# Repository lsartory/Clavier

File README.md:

# Clavier

Clavier (French for ‘keyboard’) is an FPGA-based mechanical keyboard with an integrated USB hub, and numerous communication interfaces (JTAG, SPI, I²C, UART).

## Features

- Full size 105 keys ISO keyboard + one extra
- Compatible with PCB mounted Cherry MX switches
- N-key rollover
- 1000 Hz polling rate
- No multiplexing, no ghosting
- 2-port USB 2.0 hub
- JTAG, SPI, I²C, 2 × UART, and 8 × GPIOs
- FPGA-based, VHDL only, no ALU
- Fully open-source, including all design tools (see below)

### What's the extra key for?

It's the coffee key.
Use it to lock your computer and go have a break.

It can also be long-pressed for 5 seconds to reset the FPGA.

## Required tools

- [KiCad](https://www.kicad.org) for the PCB
- [FreeCAD](https://www.freecad.org) or [OpenSCAD](https://openscad.org) for the housing
- [OSS CAD Suite](https://github.com/YosysHQ/oss-cad-suite-build) (GHDL, Yosys, hdl, ghdl-yosys-plugin, nextpnr-ecp5, ecppack, and openFPGALoader) and [GNU Make](https://www.gnu.org/software/make) for the FPGA

## PCB

The PCB has 4 layers and requires no unusual capabilities to produce.
It is however not easy to assemble by hand mostly due to 0402 passives and the FPGA in BGA packaging.

### Schematics

A PDF version of the schematics is available here, for convenience: [PCB/doc/clavier.pdf](PCB/doc/clavier.pdf).

## Housing

### Version 1

An OpenSCAD version of the housing was created first and is fine for 3D printing.
The FreeCAD version was created afterwards for exporting to STEP, which is more suitable for CNC machining.
Both alternatives are functionally equivalent.

### Version 2

The first version fits properly, but it turns out that it is not angled in a comfortable way.
To correct this, a second version was created with an angle of 8° that makes the front part much thinner.
This one is only available in FreeCAD.

## FPGA

### How to build

Simply run `make` in the FPGA subfolder.
If using OSS CAD Suite, make sure [the environment is set](https://github.com/YosysHQ/oss-cad-suite-build?tab=readme-ov-file#installation) first.

### How to program

The integrated JTAG interface can be used to program the FPGA.
The switch `SW18` is used to toggle the interfaces on or off. The LED `D1` close by displays the current status.
Connect the JTAG interface with jumper cables, then run either `make prog-sram` or `make prog-flash`, depending on if the configuration needs to be permanent or not.

## Communication interfaces

Except for the GPIOs that are connected directly to the FPGA, communications are handled by the [CH347F](https://www.lcsc.com/datasheet/C18221627.pdf).

## 3D renders

## Licenses

- The PCB and housing are licensed under the [CERN Open Hardware Licence Version 2 - Permissive](https://spdx.org/licenses/CERN-OHL-P-2.0.html).
- The FPGA code is licensed under the [MIT Licence](https://spdx.org/licenses/MIT.html).
- The pictures are licensed under the [CC BY 4.0 License](https://creativecommons.org/licenses/by/4.0/).

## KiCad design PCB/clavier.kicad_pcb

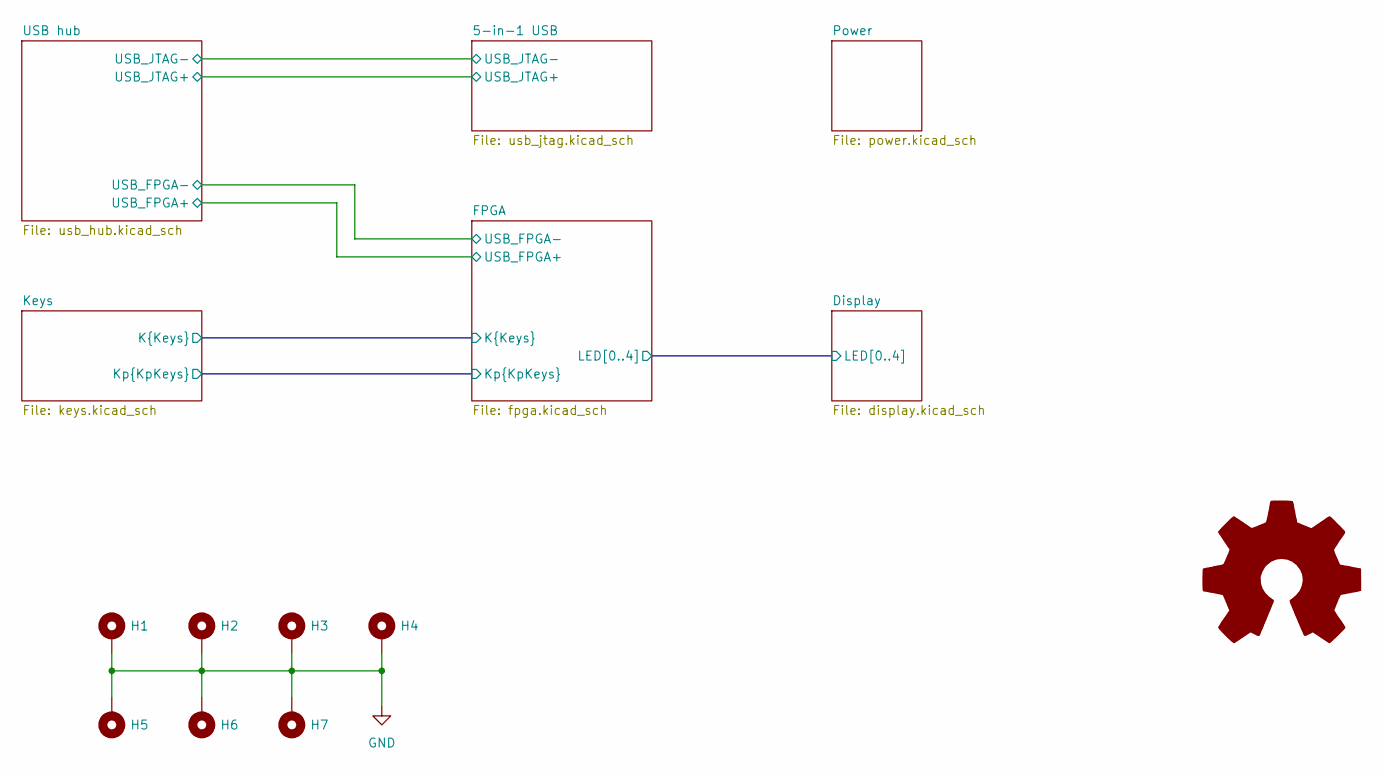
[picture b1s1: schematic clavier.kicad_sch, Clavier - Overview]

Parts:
H1, H2, H3, H4, H5, H6, H7: MountingHole_Pad; MountingHole_3.2mm_M3_ISO7380_Pad_TopBottom
OSHW1: Logo_Open_Hardware_Large; OSHW-Symbol_13.4x12mm_SilkScreen

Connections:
GND: H1.1, H2.1, H3.1, H4.1, H5.1, H6.1, H7.1; also elsewhere on the board

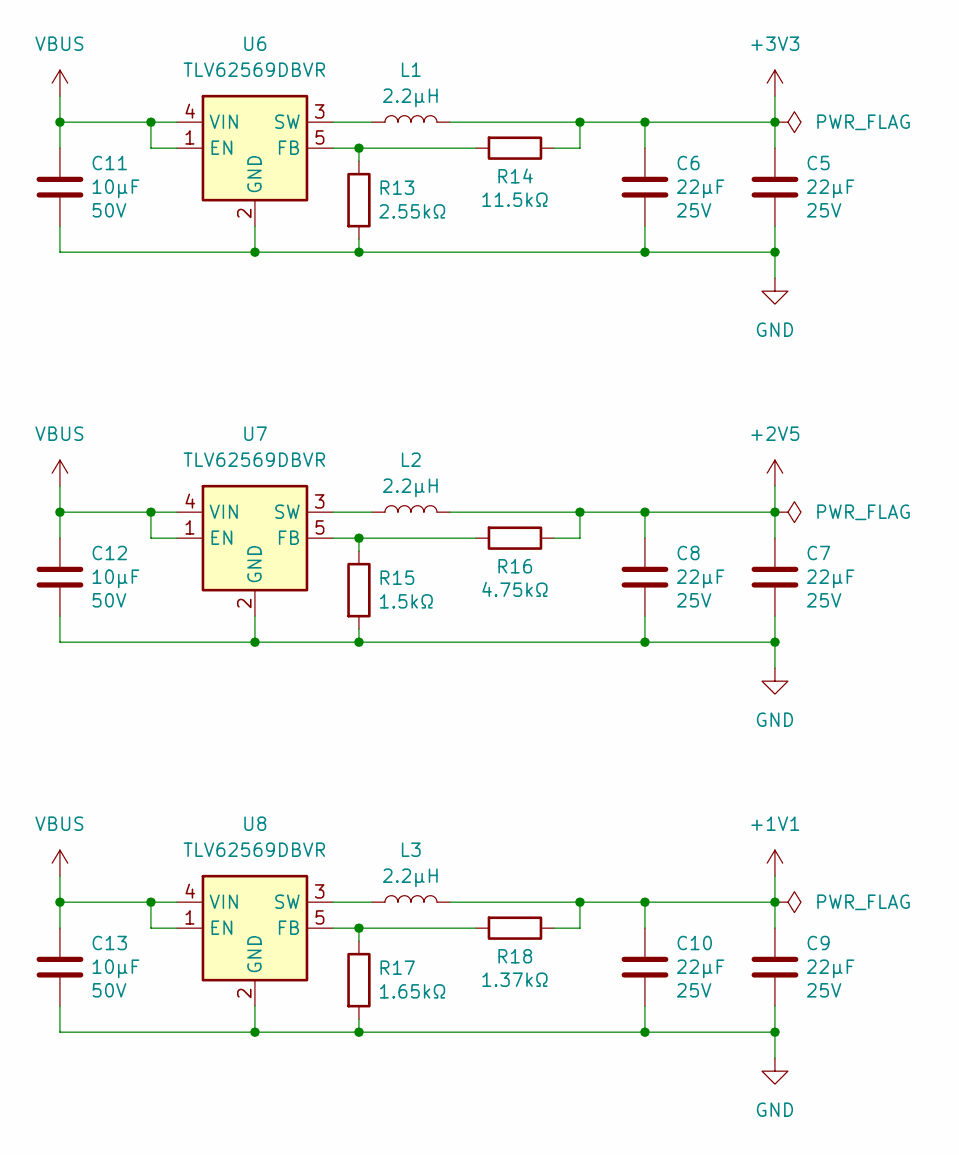
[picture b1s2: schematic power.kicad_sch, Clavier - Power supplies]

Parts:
C5, C6, C7, C8, C9, C10: 22µF; C_0805_2012Metric; Voltage 25V; Part_number GRM21BR61E226ME44L; LCSC C86816
C11, C12, C13: 10µF; C_0805_2012Metric; Voltage 50V; Part_number GRM21BR61H106KE43L; LCSC C440198
L1, L2, L3: 2.2µH; L_1210_3225Metric; Part_number DFE322520FD-2R2M=P2; LCSC C2045365
R13: 2.55kΩ; R_0402_1005Metric_Pad0.72x0.64mm_HandSolder; Part_number RC0402FR-072K55L; LCSC C185431
R14: 11.5kΩ; R_0402_1005Metric_Pad0.72x0.64mm_HandSolder; Part_number RC0402FR-0711K5L; LCSC C295874
R15: 1.5kΩ; R_0402_1005Metric_Pad0.72x0.64mm_HandSolder; Part_number RC0402FR-071K5L; LCSC C114759
R16: 4.75kΩ; R_0402_1005Metric_Pad0.72x0.64mm_HandSolder; Part_number RC0402FR-074K75L; LCSC C137966
R17: 1.65kΩ; R_0402_1005Metric_Pad0.72x0.64mm_HandSolder; Part_number RT0402BRD071K65L; LCSC C852615
R18: 1.37kΩ; R_0402_1005Metric_Pad0.72x0.64mm_HandSolder; Part_number RT0402CRE071K37L; LCSC C705664
U6, U7, U8: TLV62569DBVR; SOT-23-5; Part_number TLV62569DBVR; LCSC C141836

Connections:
+1V1: C9.1, C10.1, L3.2, R18.1; also elsewhere on the board
+2V5: C7.1, C8.1, L2.2, R16.1; also elsewhere on the board
+3V3: C5.1, C6.1, L1.2, R14.1; also elsewhere on the board
GND: C5.2, C6.2, C7.2, C8.2, C9.2, C10.2, C11.2, C12.2, C13.2, R13.2, R15.2, R17.2, U6.2 (GND), U7.2 (GND), U8.2 (GND); also elsewhere on the board
unnamed: R13.1, R14.2, U6.5 (FB)
unnamed: L1.1, U6.3 (SW)
unnamed: R15.1, R16.2, U7.5 (FB)
unnamed: L2.1, U7.3 (SW)
unnamed: R17.1, R18.2, U8.5 (FB)
unnamed: L3.1, U8.3 (SW)
VBUS: C11.1, C12.1, C13.1, U6.1 (EN), U6.4 (VIN), U7.1 (EN), U7.4 (VIN), U8.1 (EN), U8.4 (VIN); also elsewhere on the board

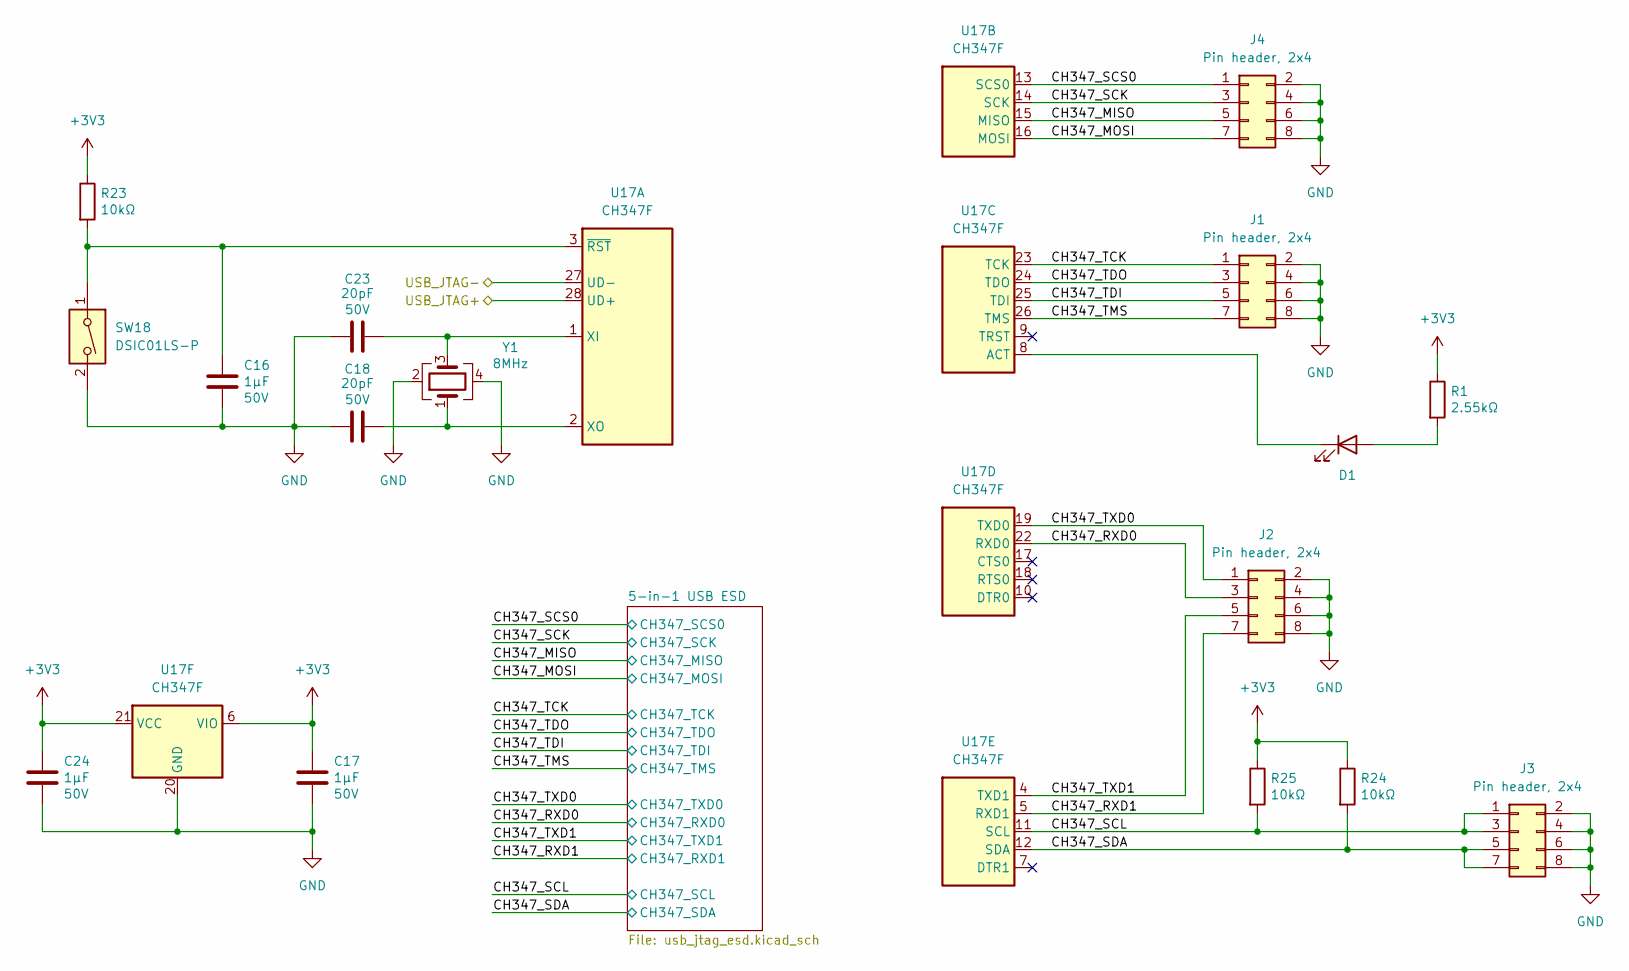
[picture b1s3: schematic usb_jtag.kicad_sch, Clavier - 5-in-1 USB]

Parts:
C16, C17, C24: 1µF; C_0402_1005Metric_Pad0.74x0.62mm_HandSolder; Voltage 50V; Part_number GRM155R61H105KE05D; LCSC C1518208
C18, C23: 20pF; C_0402_1005Metric_Pad0.74x0.62mm_HandSolder; Voltage 50V; Part_number GRM1555C1H200JA01D; LCSC C76959
D1: LED; LED_0603_1608Metric_Pad1.05x0.95mm_HandSolder; Part_number XL-1608UOC-06; LCSC C965800
J1, J2, J3, J4: Pin header, 2x4; PinHeader_2x04_P2.54mm_Vertical; Part_number ZX-PZ2.54-2-4PZZ; LCSC C7501275
R1: 2.55kΩ; R_0402_1005Metric_Pad0.72x0.64mm_HandSolder; Part_number RC0402FR-072K55L; LCSC C185431
R23, R24, R25: 10kΩ; R_0402_1005Metric_Pad0.72x0.64mm_HandSolder; Part_number RE0402DRE0710KL; LCSC C851874
SW18: DSIC01LS-P; SW_DIP_SPSTx01_Slide_6.7x4.1mm_W8.61mm_P2.54mm_LowProfile; Part_number DSIC01LS-P; LCSC C600988
U17: CH347F; QFN-28-1EP_4x4mm_P0.4mm_EP2.4x2.4mm; Part_number CH347F; LCSC C18221627
Y1: 8MHz; Crystal_SMD_3225-4Pin_3.2x2.5mm; Part_number TAXM8M4RDBCCT2T; LCSC C400090

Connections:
+3V3: C17.1, C24.1, R1.1, R23.1, R24.1, R25.1, U17.6 (VIO), U17.21 (VCC); also elsewhere on the board
/5-in-1 USB/CH347_MISO: J4.5, U17.15 (MISO); also elsewhere on the board
/5-in-1 USB/CH347_MOSI: J4.7, U17.16 (MOSI); also elsewhere on the board
/5-in-1 USB/CH347_RXD0: J2.3, U17.22 (RXD0); also elsewhere on the board
/5-in-1 USB/CH347_RXD1: J2.7, U17.5 (RXD1); also elsewhere on the board
/5-in-1 USB/CH347_SCK: J4.3, U17.14 (SCK); also elsewhere on the board
/5-in-1 USB/CH347_SCL: J3.1, J3.3, R25.2, U17.11 (SCL); also elsewhere on the board
/5-in-1 USB/CH347_SCS0: J4.1, U17.13 (SCS0); also elsewhere on the board
/5-in-1 USB/CH347_SDA: J3.5, J3.7, R24.2, U17.12 (SDA); also elsewhere on the board
/5-in-1 USB/CH347_TCK: J1.1, U17.23 (TCK); also elsewhere on the board
/5-in-1 USB/CH347_TDI: J1.5, U17.25 (TDI); also elsewhere on the board
/5-in-1 USB/CH347_TDO: J1.3, U17.24 (TDO); also elsewhere on the board
/5-in-1 USB/CH347_TMS: J1.7, U17.26 (TMS); also elsewhere on the board
/5-in-1 USB/CH347_TXD0: J2.1, U17.19 (TXD0); also elsewhere on the board
/5-in-1 USB/CH347_TXD1: J2.5, U17.4 (TXD1); also elsewhere on the board
/5-in-1 USB/USB_JTAG+: U17.28 (UD+); also elsewhere on the board
/5-in-1 USB/USB_JTAG-: U17.27 (UD-); also elsewhere on the board
GND: C16.2, C17.2, C18.1, C23.1, C24.2, J1.2, J1.4, J1.6, J1.8, J2.2, J2.4, J2.6, J2.8, J3.2, J3.4, J3.6, J3.8, J4.2, J4.4, J4.6, J4.8, SW18.2, U17.20 (GND), U17.29 (GND), Y1.2, Y1.4; also elsewhere on the board
unnamed: D1.2 (A), R1.2
unnamed: D1.1 (K), U17.8 (ACT)
unnamed: C23.2, U17.1 (XI), Y1.3
unnamed: C18.2, U17.2 (XO), Y1.1
unnamed: C16.1, R23.2, SW18.1, U17.3 (~RST)

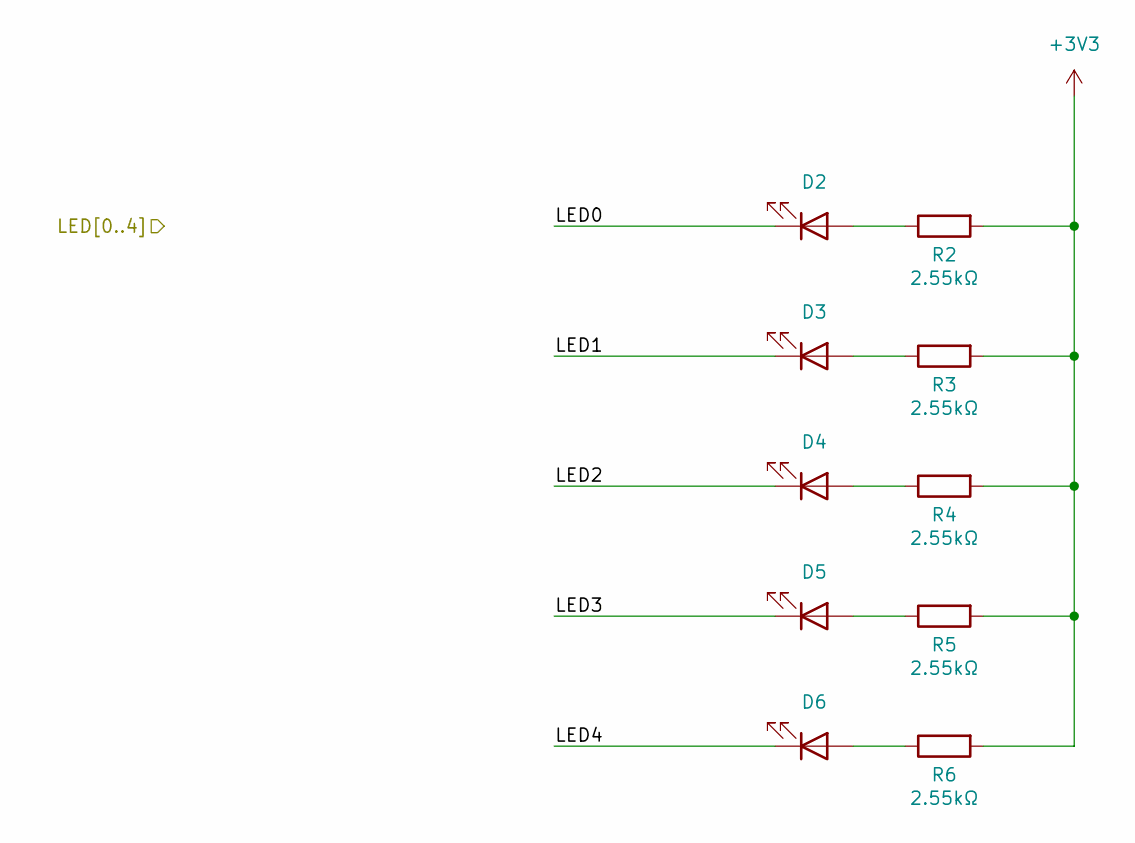
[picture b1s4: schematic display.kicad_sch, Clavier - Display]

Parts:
D2, D3, D4, D5, D6: LED; LED_0603_1608Metric_Pad1.05x0.95mm_HandSolder; Part_number XL-1608UOC-06; LCSC C965800
R2, R3, R4, R5, R6: 2.55kΩ; R_0402_1005Metric_Pad0.72x0.64mm_HandSolder; Part_number RC0402FR-072K55L; LCSC C185431

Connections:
+3V3: R2.2, R3.2, R4.2, R5.2, R6.2; also elsewhere on the board
/Display/LED0: D2.1 (K); also elsewhere on the board
/Display/LED1: D3.1 (K); also elsewhere on the board
/Display/LED2: D4.1 (K); also elsewhere on the board
/Display/LED3: D5.1 (K); also elsewhere on the board
/Display/LED4: D6.1 (K); also elsewhere on the board
unnamed: D2.2 (A), R2.1
unnamed: D3.2 (A), R3.1
unnamed: D4.2 (A), R4.1
unnamed: D5.2 (A), R5.1
unnamed: D6.2 (A), R6.1

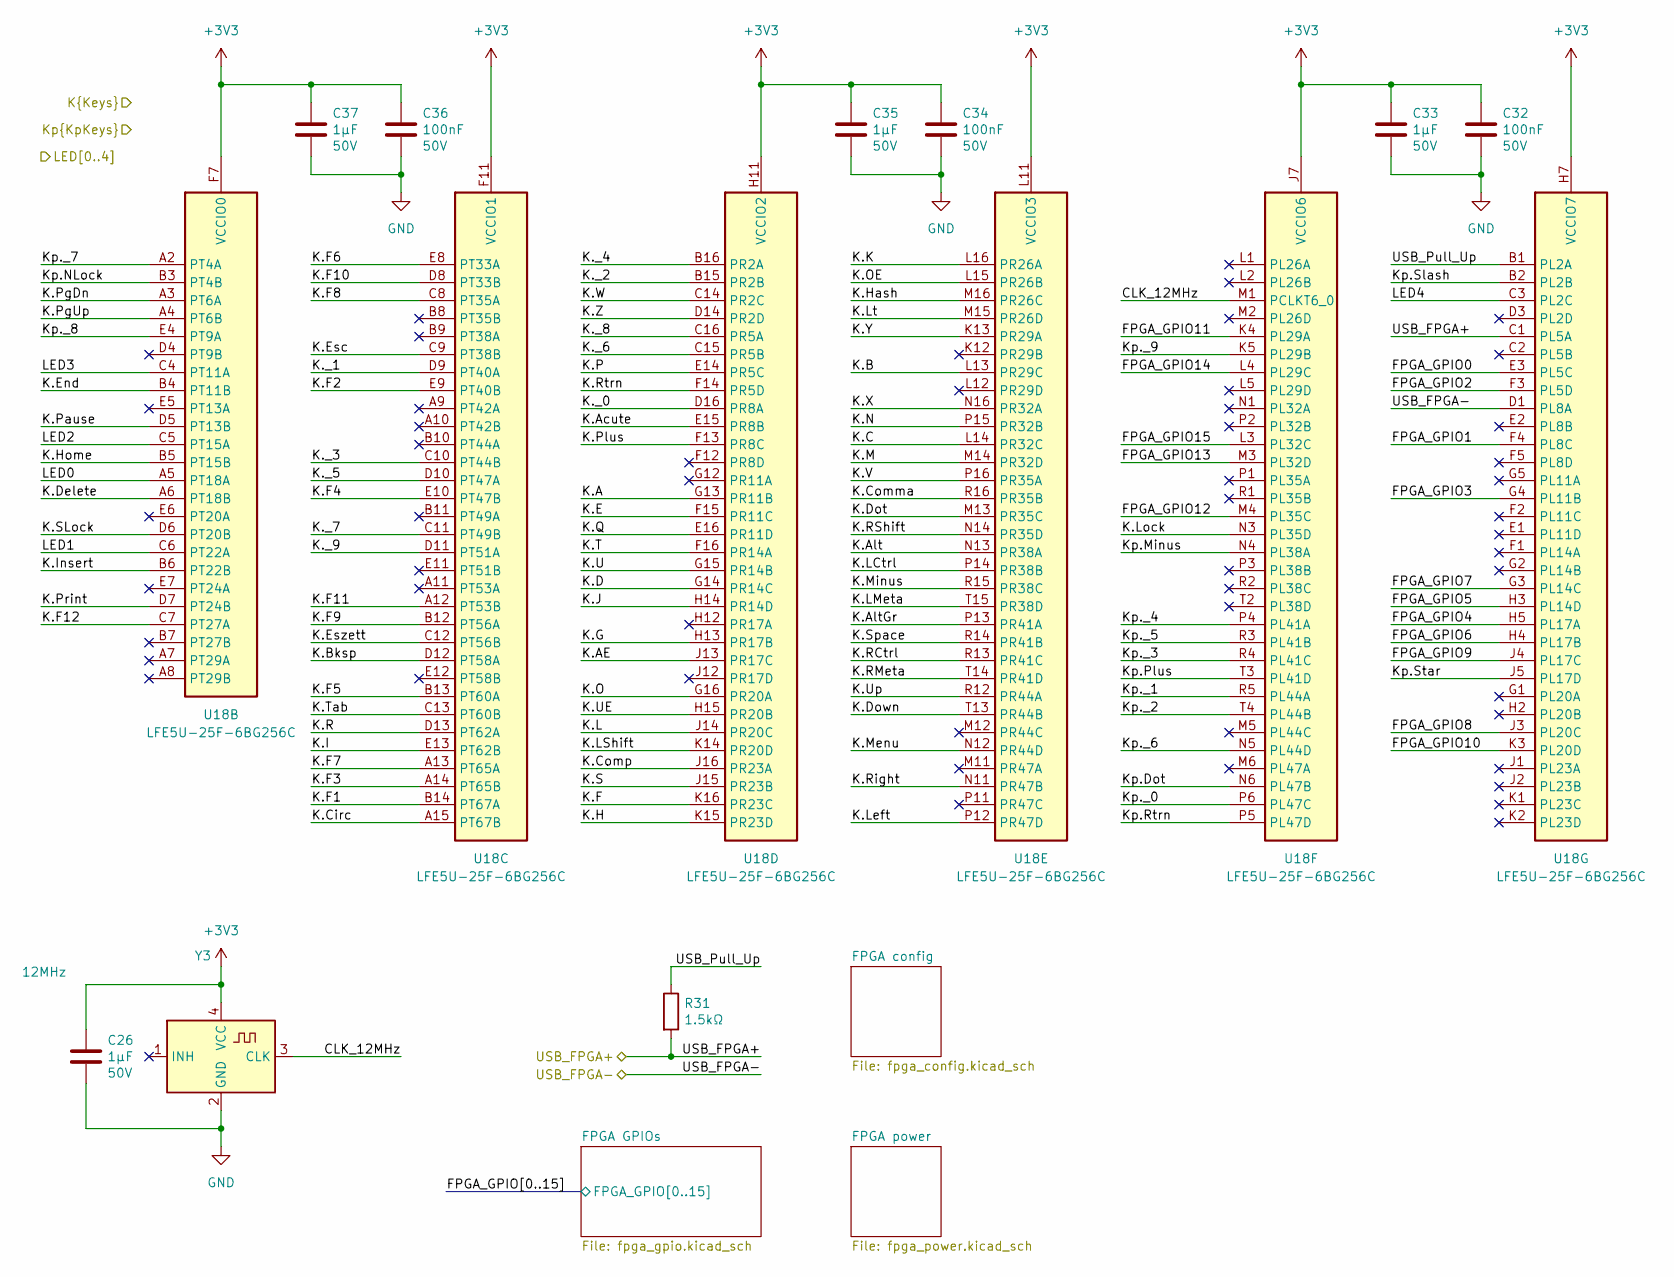
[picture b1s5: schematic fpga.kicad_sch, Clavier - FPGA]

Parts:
C26, C33, C35, C37: 1µF; C_0402_1005Metric_Pad0.74x0.62mm_HandSolder; Voltage 50V; Part_number GRM155R61H105KE05D; LCSC C1518208
C32, C34, C36: 100nF; C_0402_1005Metric_Pad0.74x0.62mm_HandSolder; Voltage 50V; Part_number GRM155R71H104KE14D; LCSC C77020
R31: 1.5kΩ; R_0402_1005Metric_Pad0.72x0.64mm_HandSolder; Part_number RC0402FR-071K5L; LCSC C114759
U18: LFE5U-25F-6BG256C; BGA-256_14.0x14.0mm_Layout16x16_P0.8mm_Ball0.45mm_Pad0.32mm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; Part_number LFE5U-25F-6BG256C; LCSC C1521614
Y3: 12MHz; Crystal_SMD_2520-4Pin_2.5x2.0mm; Part_number CO22H4-12.000-WPGDTSNL; LCSC C3034288

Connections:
+3V3: C26.1, C32.1, C33.1, C34.1, C35.1, C36.1, C37.1, U18.F6 (VCCIO0), U18.F7 (VCCIO0), U18.F10 (VCCIO1), U18.F11 (VCCIO1), U18.H6 (VCCIO7), U18.H7 (VCCIO7), U18.H11 (VCCIO2), U18.J6 (VCCIO6), U18.J7 (VCCIO6), U18.J11 (VCCIO2), U18.K11 (VCCIO3), U18.L11 (VCCIO3), Y3.4 (VCC); also elsewhere on the board
/Display/LED0: U18.A5 (PT18A); also elsewhere on the board
/Display/LED1: U18.C6 (PT22A); also elsewhere on the board
/Display/LED2: U18.C5 (PT15A); also elsewhere on the board
/Display/LED3: U18.C4 (PT11A); also elsewhere on the board
/Display/LED4: U18.C3 (PL2C); also elsewhere on the board
/FPGA/CLK_12MHz: U18.M1 (PCLKT6_0), Y3.3 (CLK)
/FPGA/FPGA_GPIO0: U18.E3 (PL5C); also elsewhere on the board
/FPGA/FPGA_GPIO1: U18.F4 (PL8C); also elsewhere on the board
/FPGA/FPGA_GPIO2: U18.F3 (PL5D); also elsewhere on the board
/FPGA/FPGA_GPIO3: U18.G4 (PL11B); also elsewhere on the board
/FPGA/FPGA_GPIO4: U18.H5 (PL17A); also elsewhere on the board
/FPGA/FPGA_GPIO5: U18.H3 (PL14D); also elsewhere on the board
/FPGA/FPGA_GPIO6: U18.H4 (PL17B); also elsewhere on the board
/FPGA/FPGA_GPIO7: U18.G3 (PL14C); also elsewhere on the board
/FPGA/FPGA_GPIO8: U18.J3 (PL20C); also elsewhere on the board
/FPGA/FPGA_GPIO9: U18.J4 (PL17C); also elsewhere on the board
/FPGA/FPGA_GPIO10: U18.K3 (PL20D); also elsewhere on the board
/FPGA/FPGA_GPIO11: U18.K4 (PL29A); also elsewhere on the board
/FPGA/FPGA_GPIO12: U18.M4 (PL35C); also elsewhere on the board
/FPGA/FPGA_GPIO13: U18.M3 (PL32D); also elsewhere on the board
/FPGA/FPGA_GPIO14: U18.L4 (PL29C); also elsewhere on the board
/FPGA/FPGA_GPIO15: U18.L3 (PL32C); also elsewhere on the board
/FPGA/K.A: U18.G13 (PR11B); also elsewhere on the board
/FPGA/K.AE: U18.J13 (PR17C); also elsewhere on the board
/FPGA/K.Acute: U18.E15 (PR8B); also elsewhere on the board
/FPGA/K.Alt: U18.N13 (PR38A); also elsewhere on the board
/FPGA/K.AltGr: U18.P13 (PR41A); also elsewhere on the board
/FPGA/K.B: U18.L13 (PR29C); also elsewhere on the board
/FPGA/K.Bksp: U18.D12 (PT58A); also elsewhere on the board
/FPGA/K.C: U18.L14 (PR32C); also elsewhere on the board
/FPGA/K.Circ: U18.A15 (PT67B); also elsewhere on the board
/FPGA/K.Comma: U18.R16 (PR35B); also elsewhere on the board
/FPGA/K.Comp: U18.J16 (PR23A); also elsewhere on the board
/FPGA/K.D: U18.G14 (PR14C); also elsewhere on the board
/FPGA/K.Delete: U18.A6 (PT18B); also elsewhere on the board
/FPGA/K.Dot: U18.M13 (PR35C); also elsewhere on the board
/FPGA/K.Down: U18.T13 (PR44B); also elsewhere on the board
/FPGA/K.E: U18.F15 (PR11C); also elsewhere on the board
/FPGA/K.End: U18.B4 (PT11B); also elsewhere on the board
/FPGA/K.Esc: U18.C9 (PT38B); also elsewhere on the board
/FPGA/K.Eszett: U18.C12 (PT56B); also elsewhere on the board
/FPGA/K.F: U18.K16 (PR23C); also elsewhere on the board
/FPGA/K.F1: U18.B14 (PT67A); also elsewhere on the board
/FPGA/K.F2: U18.E9 (PT40B); also elsewhere on the board
/FPGA/K.F3: U18.A14 (PT65B); also elsewhere on the board
/FPGA/K.F4: U18.E10 (PT47B); also elsewhere on the board
/FPGA/K.F5: U18.B13 (PT60A); also elsewhere on the board
/FPGA/K.F6: U18.E8 (PT33A); also elsewhere on the board
/FPGA/K.F7: U18.A13 (PT65A); also elsewhere on the board
/FPGA/K.F8: U18.C8 (PT35A); also elsewhere on the board
/FPGA/K.F9: U18.B12 (PT56A); also elsewhere on the board
/FPGA/K.F10: U18.D8 (PT33B); also elsewhere on the board
/FPGA/K.F11: U18.A12 (PT53B); also elsewhere on the board
/FPGA/K.F12: U18.C7 (PT27A); also elsewhere on the board
/FPGA/K.G: U18.H13 (PR17B); also elsewhere on the board
/FPGA/K.H: U18.K15 (PR23D); also elsewhere on the board
/FPGA/K.Hash: U18.M16 (PR26C); also elsewhere on the board
/FPGA/K.Home: U18.B5 (PT15B); also elsewhere on the board
/FPGA/K.I: U18.E13 (PT62B); also elsewhere on the board
/FPGA/K.Insert: U18.B6 (PT22B); also elsewhere on the board
/FPGA/K.J: U18.H14 (PR14D); also elsewhere on the board
/FPGA/K.K: U18.L16 (PR26A); also elsewhere on the board
/FPGA/K.L: U18.J14 (PR20C); also elsewhere on the board
/FPGA/K.LCtrl: U18.P14 (PR38B); also elsewhere on the board
/FPGA/K.LMeta: U18.T15 (PR38D); also elsewhere on the board
/FPGA/K.LShift: U18.K14 (PR20D); also elsewhere on the board
/FPGA/K.Left: U18.P12 (PR47D); also elsewhere on the board
/FPGA/K.Lock: U18.N3 (PL35D); also elsewhere on the board
/FPGA/K.Lt: U18.M15 (PR26D); also elsewhere on the board
/FPGA/K.M: U18.M14 (PR32D); also elsewhere on the board
/FPGA/K.Menu: U18.N12 (PR44D); also elsewhere on the board
/FPGA/K.Minus: U18.R15 (PR38C); also elsewhere on the board
/FPGA/K.N: U18.P15 (PR32B); also elsewhere on the board
/FPGA/K.O: U18.G16 (PR20A); also elsewhere on the board
/FPGA/K.OE: U18.L15 (PR26B); also elsewhere on the board
/FPGA/K.P: U18.E14 (PR5C); also elsewhere on the board
/FPGA/K.Pause: U18.D5 (PT13B); also elsewhere on the board
/FPGA/K.PgDn: U18.A3 (PT6A); also elsewhere on the board
/FPGA/K.PgUp: U18.A4 (PT6B); also elsewhere on the board
/FPGA/K.Plus: U18.F13 (PR8C); also elsewhere on the board
/FPGA/K.Print: U18.D7 (PT24B); also elsewhere on the board
/FPGA/K.Q: U18.E16 (PR11D); also elsewhere on the board
/FPGA/K.R: U18.D13 (PT62A); also elsewhere on the board
/FPGA/K.RCtrl: U18.R13 (PR41C); also elsewhere on the board
/FPGA/K.RMeta: U18.T14 (PR41D); also elsewhere on the board
/FPGA/K.RShift: U18.N14 (PR35D); also elsewhere on the board
/FPGA/K.Right: U18.N11 (PR47B); also elsewhere on the board
/FPGA/K.Rtrn: U18.F14 (PR5D); also elsewhere on the board
/FPGA/K.S: U18.J15 (PR23B); also elsewhere on the board
/FPGA/K.SLock: U18.D6 (PT20B); also elsewhere on the board
/FPGA/K.Space: U18.R14 (PR41B); also elsewhere on the board
/FPGA/K.T: U18.F16 (PR14A); also elsewhere on the board
/FPGA/K.Tab: U18.C13 (PT60B); also elsewhere on the board
/FPGA/K.U: U18.G15 (PR14B); also elsewhere on the board
/FPGA/K.UE: U18.H15 (PR20B); also elsewhere on the board
/FPGA/K.Up: U18.R12 (PR44A); also elsewhere on the board
/FPGA/K.V: U18.P16 (PR35A); also elsewhere on the board
/FPGA/K.W: U18.C14 (PR2C); also elsewhere on the board
/FPGA/K.X: U18.N16 (PR32A); also elsewhere on the board
/FPGA/K.Y: U18.K13 (PR29A); also elsewhere on the board
/FPGA/K.Z: U18.D14 (PR2D); also elsewhere on the board
/FPGA/K._0: U18.D16 (PR8A); also elsewhere on the board
/FPGA/K._1: U18.D9 (PT40A); also elsewhere on the board
/FPGA/K._2: U18.B15 (PR2B); also elsewhere on the board
/FPGA/K._3: U18.C10 (PT44B); also elsewhere on the board
/FPGA/K._4: U18.B16 (PR2A); also elsewhere on the board
/FPGA/K._5: U18.D10 (PT47A); also elsewhere on the board
/FPGA/K._6: U18.C15 (PR5B); also elsewhere on the board
/FPGA/K._7: U18.C11 (PT49B); also elsewhere on the board
/FPGA/K._8: U18.C16 (PR5A); also elsewhere on the board
/FPGA/K._9: U18.D11 (PT51A); also elsewhere on the board
/FPGA/Kp.Dot: U18.N6 (PL47B); also elsewhere on the board
/FPGA/Kp.Minus: U18.N4 (PL38A); also elsewhere on the board
/FPGA/Kp.NLock: U18.B3 (PT4B); also elsewhere on the board
/FPGA/Kp.Plus: U18.T3 (PL41D); also elsewhere on the board
/FPGA/Kp.Rtrn: U18.P5 (PL47D); also elsewhere on the board
/FPGA/Kp.Slash: U18.B2 (PL2B); also elsewhere on the board
/FPGA/Kp.Star: U18.J5 (PL17D); also elsewhere on the board
/FPGA/Kp._0: U18.P6 (PL47C); also elsewhere on the board
/FPGA/Kp._1: U18.R5 (PL44A); also elsewhere on the board
/FPGA/Kp._2: U18.T4 (PL44B); also elsewhere on the board
/FPGA/Kp._3: U18.R4 (PL41C); also elsewhere on the board
/FPGA/Kp._4: U18.P4 (PL41A); also elsewhere on the board
/FPGA/Kp._5: U18.R3 (PL41B); also elsewhere on the board
/FPGA/Kp._6: U18.N5 (PL44D); also elsewhere on the board
/FPGA/Kp._7: U18.A2 (PT4A); also elsewhere on the board
/FPGA/Kp._8: U18.E4 (PT9A); also elsewhere on the board
/FPGA/Kp._9: U18.K5 (PL29B); also elsewhere on the board
/FPGA/USB_FPGA+: R31.2, U18.C1 (PL5A); also elsewhere on the board
/FPGA/USB_FPGA-: U18.D1 (PL8A); also elsewhere on the board
/FPGA/USB_Pull_Up: R31.1, U18.B1 (PL2A)
GND: C26.2, C32.2, C33.2, C34.2, C35.2, C36.2, C37.2, Y3.2 (GND); also elsewhere on the board

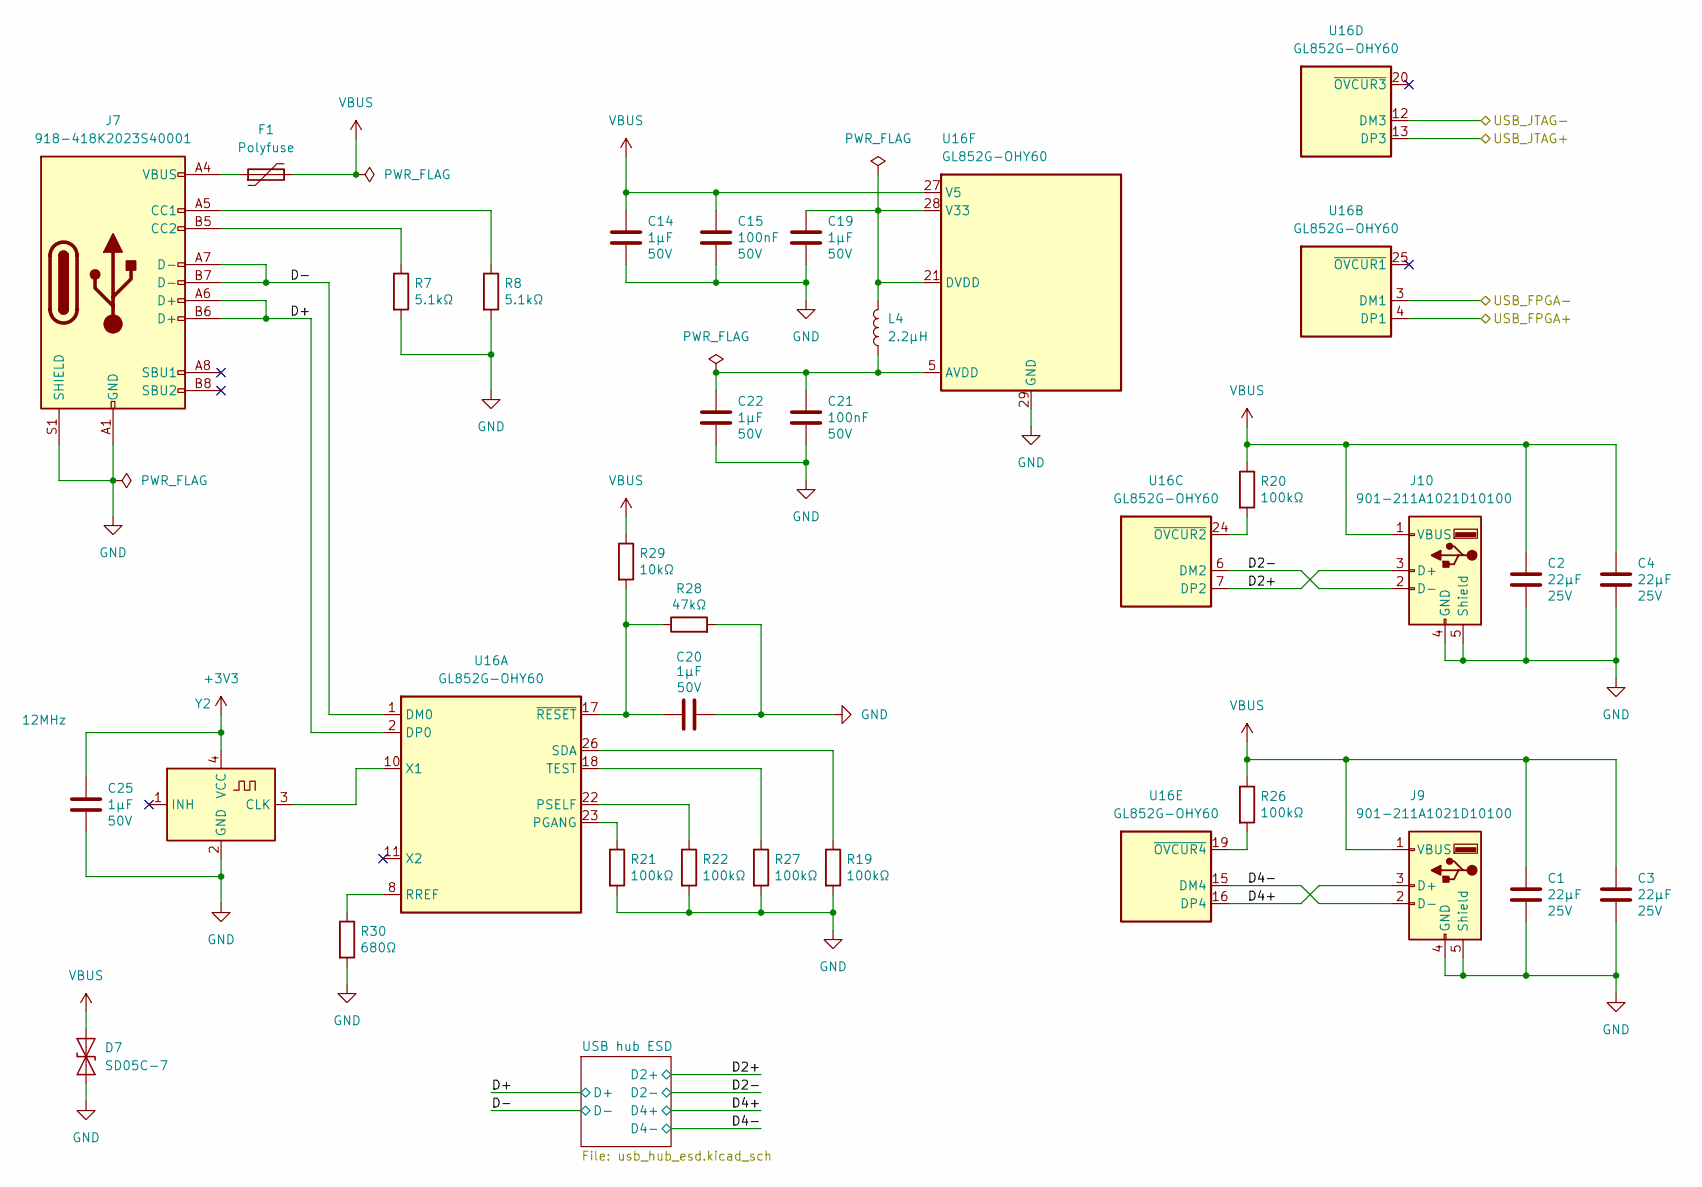
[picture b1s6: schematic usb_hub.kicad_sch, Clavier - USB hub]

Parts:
C1, C2, C3, C4: 22µF; C_0805_2012Metric; Voltage 25V; Part_number GRM21BR61E226ME44L; LCSC C86816
C14, C19, C20, C22, C25: 1µF; C_0402_1005Metric_Pad0.74x0.62mm_HandSolder; Voltage 50V; Part_number GRM155R61H105KE05D; LCSC C1518208
C15, C21: 100nF; C_0402_1005Metric_Pad0.74x0.62mm_HandSolder; Voltage 50V; Part_number GRM155R71H104KE14D; LCSC C77020
D7: SD05C-7; D_SOD-323; Part_number SD05C-7; LCSC C1869324
F1: Polyfuse; Fuse_0805_2012Metric_Pad1.15x1.40mm_HandSolder; Part_number BSMD0805-075-12V; LCSC C883111
J7: 918-418K2023S40001; USB_C_Receptacle_GCT_USB4105-xx-A_16P_TopMnt_Horizontal; Part_number 918-418K2023S40001; LCSC C167321
J9, J10: 901-211A1021D10100; USB_A_Molex_67643_Horizontal; Part_number 901-211A1021D10100; LCSC C2346
L4: 2.2µH; L_1210_3225Metric; Part_number DFE322520FD-2R2M=P2; LCSC C2045365
R7, R8: 5.1kΩ; R_0402_1005Metric_Pad0.72x0.64mm_HandSolder; Part_number RC0402FR-075K1L; LCSC C105872
R19, R20, R21, R22, R26, R27: 100kΩ; R_0402_1005Metric_Pad0.72x0.64mm_HandSolder; Part_number RE0402DRE07100KL; LCSC C851870
R28: 47kΩ; R_0402_1005Metric_Pad0.72x0.64mm_HandSolder; Part_number RE0402DRE0747KL; LCSC C851995
R29: 10kΩ; R_0402_1005Metric_Pad0.72x0.64mm_HandSolder; Part_number RE0402DRE0710KL; LCSC C851874
R30: 680Ω; R_0402_1005Metric_Pad0.72x0.64mm_HandSolder; Part_number RC0402FR-07680RL; LCSC C137948
U16: GL852G-OHY60; QFN-28-1EP_5x5mm_P0.5mm_EP3.75x3.75mm; Part_number GL852G-OHY60; LCSC C7501404
Y2: 12MHz; Crystal_SMD_2520-4Pin_2.5x2.0mm; Part_number CO22H4-12.000-WPGDTSNL; LCSC C3034288

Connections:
+3V3: C25.1, Y2.4 (VCC); also elsewhere on the board
/5-in-1 USB/USB_JTAG+: U16.13 (DP3); also elsewhere on the board
/5-in-1 USB/USB_JTAG-: U16.12 (DM3); also elsewhere on the board
/FPGA/USB_FPGA+: U16.4 (DP1); also elsewhere on the board
/FPGA/USB_FPGA-: U16.3 (DM1); also elsewhere on the board
/USB hub/D2+: J10.3 (D+), U16.7 (DP2); also elsewhere on the board
/USB hub/D2-: J10.2 (D-), U16.6 (DM2); also elsewhere on the board
/USB hub/D4+: J9.3 (D+), U16.16 (DP4); also elsewhere on the board
/USB hub/D4-: J9.2 (D-), U16.15 (DM4); also elsewhere on the board
/USB hub/D+: J7.A6 (D+), J7.B6 (D+), U16.2 (DP0); also elsewhere on the board
/USB hub/D-: J7.A7 (D-), J7.B7 (D-), U16.1 (DM0); also elsewhere on the board
AVDD: C21.1, C22.1, L4.1, U16.5 (AVDD), U16.9 (AVDD), U16.14 (AVDD)
GND: C1.2, C2.2, C3.2, C4.2, C14.2, C15.2, C19.2, C20.2, C21.2, C22.2, C25.2, D7.1 (A1), J7.A1 (GND), J7.A12 (GND), J7.B1 (GND), J7.B12 (GND), J7.S1 (SHIELD), J9.4 (GND), J9.5 (Shield), J10.4 (GND), J10.5 (Shield), R7.2, R8.2, R19.2, R21.2, R22.2, R27.2, R28.2, R30.2, U16.29 (GND), Y2.2 (GND); also elsewhere on the board
unnamed: F1.1, J7.A4 (VBUS), J7.A9 (VBUS), J7.B4 (VBUS), J7.B9 (VBUS)
unnamed: J7.A5 (CC1), R8.1
unnamed: J7.B5 (CC2), R7.1
unnamed: R21.1, U16.23 (PGANG)
unnamed: R22.1, U16.22 (PSELF)
unnamed: R30.1, U16.8 (RREF)
unnamed: R19.1, U16.26 (SDA)
unnamed: R27.1, U16.18 (TEST)
unnamed: U16.10 (X1), Y2.3 (CLK)
unnamed: C20.1, R28.1, R29.2, U16.17 (~RESET)
unnamed: R20.2, U16.24 (~OVCUR2)
unnamed: R26.2, U16.19 (~OVCUR4)
unnamed: C19.1, L4.2, U16.21 (DVDD), U16.28 (V33)
VBUS: C1.1, C2.1, C3.1, C4.1, C14.1, C15.1, D7.2 (A2), F1.2, J9.1 (VBUS), J10.1 (VBUS), R20.1, R26.1, R29.1, U16.27 (V5); also elsewhere on the board

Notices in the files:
PCB/clavier.kicad_pcb:
Copyright (c) 2025 L. Sartory
SPDX-License-Identifier: CERN-OHL-P-2.0
